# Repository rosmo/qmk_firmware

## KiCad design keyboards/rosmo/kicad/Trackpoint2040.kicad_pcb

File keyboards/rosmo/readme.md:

# RP2040 keyboard with Trackpoint and three buttons

## Layout

### Layer 1 

| Left key          | Middle Key  | Right key          | Left button                  | Right button               | Wheel up  | Wheel down  | Wheel click |
|-------------------|-------------|--------------------|------------------------------|----------------------------|-----------|-------------|-------------|
| Left mouse button | Scroll mode | Right mouse button | Volume down / Layer 3 (held) | Volume up / Layer 4 (held) | Scroll up | Scroll down | Layer 2     |

### Layer 2 (scroll pg up/dn)

| Left key          | Middle Key  | Right key          | Left button | Right button | Wheel up | Wheel down | Wheel click |
|-------------------|-------------|--------------------|-------------|--------------|----------|------------|-------------|
| Left mouse button | Scroll mode | Right mouse button | -           | -            | Page up  | Page down  | -           |

### Layer 3 (config 1)

| Left key      | Middle Key    | Right key   | Left button | Right button  | Wheel up  | Wheel down  | Wheel click |
|---------------|---------------|-------------|-------------|---------------|-----------|-------------|-------------|
| Default scale | Sniping scale | Scroll size | -           | Invert scroll | Adjust up | Adjust down | Dump config |

### Layer 4 (config 2)

| Left key       | Middle Key         | Right key         | Left button | Right button | Wheel up | Wheel down | Wheel click |
|----------------|--------------------|-------------------|-------------|--------------|----------|------------|-------------|
| Toggle sniping | Toggle drag scroll | Cycle scroll lock | Save        | -            | -        | -          | Reset       |

(Use scroll wheel to adjust scaling etc)

## Building firmware

Easiest is to use the supplied Makefile:

```sh
make -f keyboards/rosmo/Makefile
```

Keep right push button pressed to trigger Bootmagic.

## Hardware

- 6 buttons: 3 mouse buttons, scroll wheel click, 2 push-buttons for layers
- USB-C breakout

Horrible KiCad files available in [kicad/](kicad/).

3D printable case available in [case/](case/) (Adobe Fusion).

### Bill of Materials

| Reference   | Qty | Component                             |
|-------------|-----|---------------------------------------|
| D1,D2       | 2   | Diode 1N4148                          |
| ENC1        | 1   | Roller Encoder Panasonic EVQWGD001    |
| J1,J2       | 2   | 12 pin header 2.54mm pitch female     |
| SW1,SW2,SW3 | 3   | Low-profile hotswap keycap socket     |
| SW4,SW5     | 2   | Switch THT 6mm                        |
| USB_PORT1   | 1   | USB-C receptacle XKB-U262-16XN-4BVC11 |

+ USB-C connector module (male), plus some wire
+ [Holykeebs Trackpoint module](https://holykeebs.com/products/trackpoint-module)

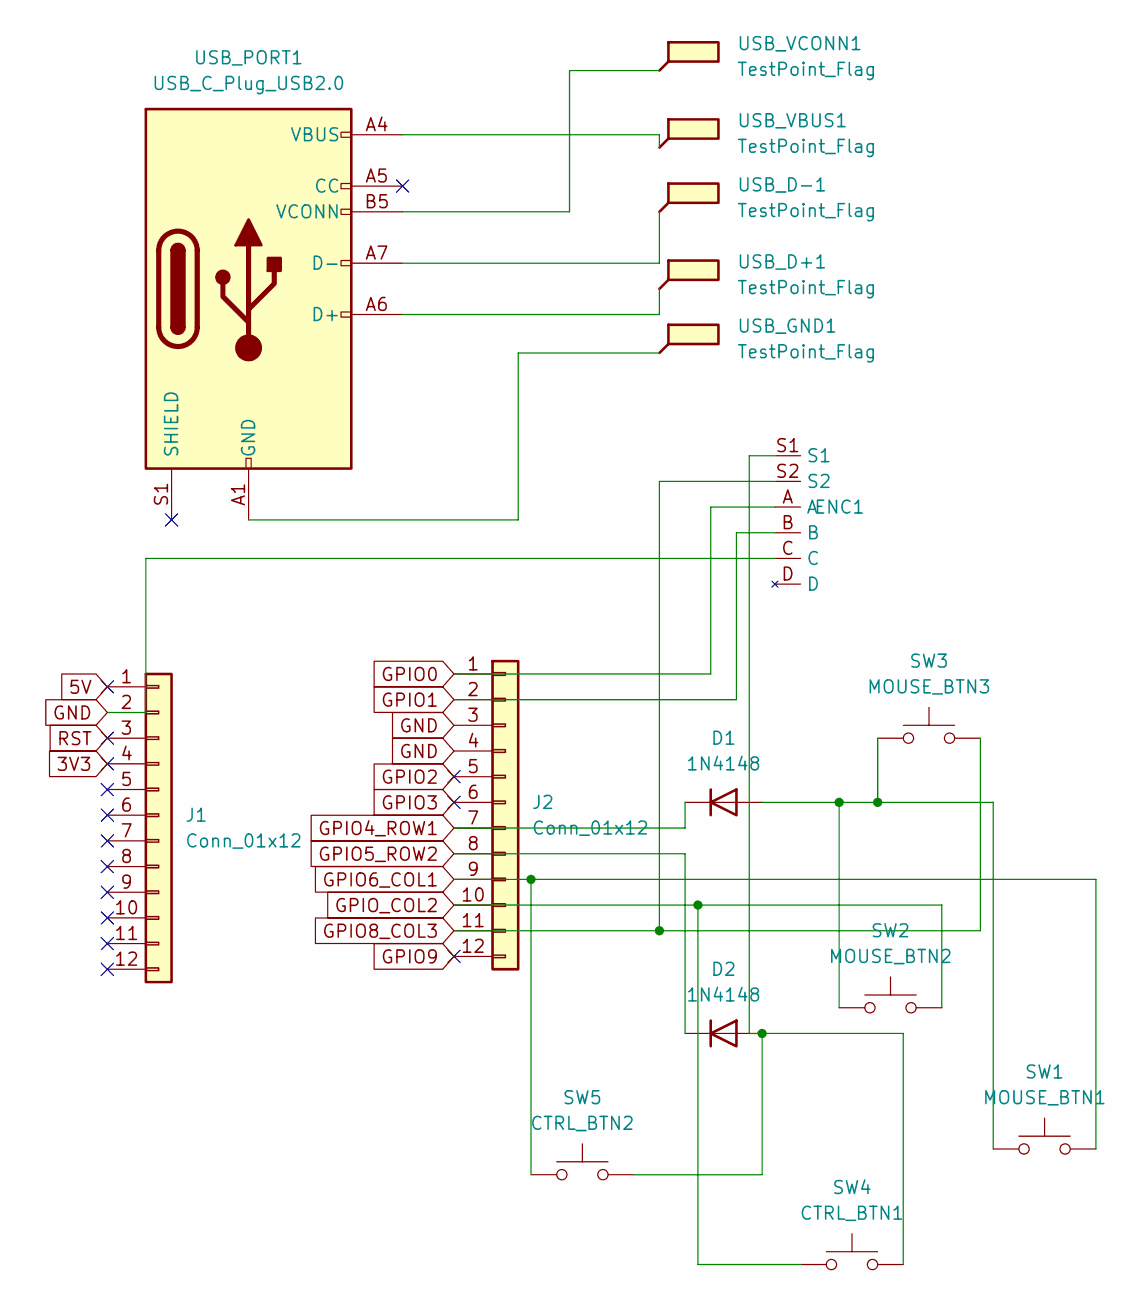
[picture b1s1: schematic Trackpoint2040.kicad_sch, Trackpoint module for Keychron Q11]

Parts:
D1, D2: 1N4148; D_DO-35_SOD27_P7.62mm_Horizontal
ENC1: RollerEncoder_Panasonic_EVQWGD001
J1, J2: Conn_01x12; PinHeader_1x12_P2.54mm_Vertical
SW1: MOUSE_BTN1; SW_Gateron_LowProfile_HotSwap_PTH
SW2: MOUSE_BTN2; SW_Gateron_LowProfile_HotSwap_PTH
SW3: MOUSE_BTN3; SW_Gateron_LowProfile_HotSwap_PTH
SW4: CTRL_BTN1; SW_PUSH_6mm
SW5: CTRL_BTN2; SW_PUSH_6mm
USB_D+1: TestPoint_Flag; TestPoint_Pad_2.0x2.0mm
USB_D-1: TestPoint_Flag; TestPoint_Pad_2.0x2.0mm
USB_GND1: TestPoint_Flag; TestPoint_Pad_2.0x2.0mm
USB_PORT1: USB_C_Plug_USB2.0; USB_C_Receptacle_XKB_U262-16XN-4BVC11
USB_VBUS1: TestPoint_Flag; TestPoint_Pad_2.0x2.0mm
USB_VCONN1: TestPoint_Flag; TestPoint_Pad_2.0x2.0mm

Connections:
3V3: J1.4
5V: J1.1
GND: ENC1.C, J1.2, J2.3, J2.4
GPIO0: ENC1.A, J2.1
GPIO1: ENC1.B, J2.2
GPIO2: J2.5
GPIO3: J2.6
GPIO4_ROW1: D1.1 (K), J2.7
GPIO5_ROW2: D2.1 (K), J2.8
GPIO6_COL1: J2.9, SW1.2, SW5.1
GPIO8_COL3: ENC1.S2, J2.11, SW3.2
GPIO9: J2.12
GPIO_COL2: J2.10, SW2.2, SW4.1
unnamed: D1.2 (A), SW1.1, SW2.1, SW3.1
unnamed: D2.2 (A), ENC1.S1, SW4.2, SW5.2
unnamed: USB_GND1.1, USB_PORT1.A1 (GND), USB_PORT1.A12 (GND), USB_PORT1.B1 (GND), USB_PORT1.B12 (GND)
unnamed: USB_D+1.1, USB_PORT1.A6 (D+)
unnamed: USB_D-1.1, USB_PORT1.A7 (D-)
unnamed: USB_PORT1.A4 (VBUS), USB_PORT1.A9 (VBUS), USB_PORT1.B4 (VBUS), USB_PORT1.B9 (VBUS), USB_VBUS1.1
unnamed: USB_PORT1.B5 (VCONN), USB_VCONN1.1
RST: J1.3

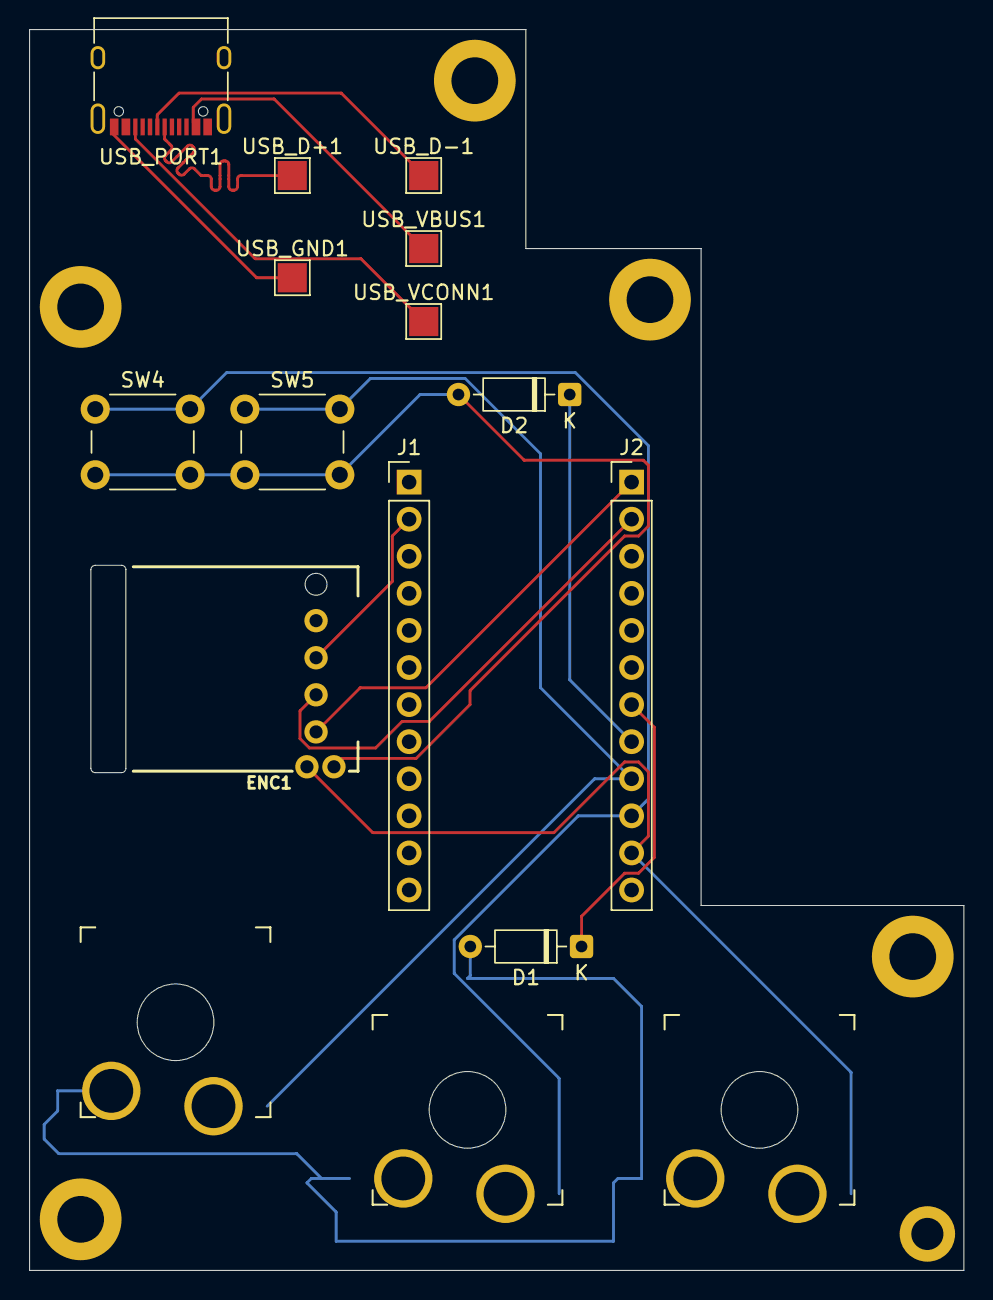
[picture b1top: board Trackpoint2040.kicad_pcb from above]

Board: 2 copper layers, 64.0 x 85.0 mm, 16 parts (0 on the bottom side), 15 nets.

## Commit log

2026-02-28 Add rosmo keyboard
2026-04-03 Update keyboard files
2026-04-05 Keymap changes, add docs, add KiCad files
2026-04-05 Add missing image
2026-04-05 Add Fusion files for case
